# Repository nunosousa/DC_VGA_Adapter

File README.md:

# DC_VGA_Adapter
This is a project detailing a Dreamcast VGA circuit adapter to provide VGA video output.

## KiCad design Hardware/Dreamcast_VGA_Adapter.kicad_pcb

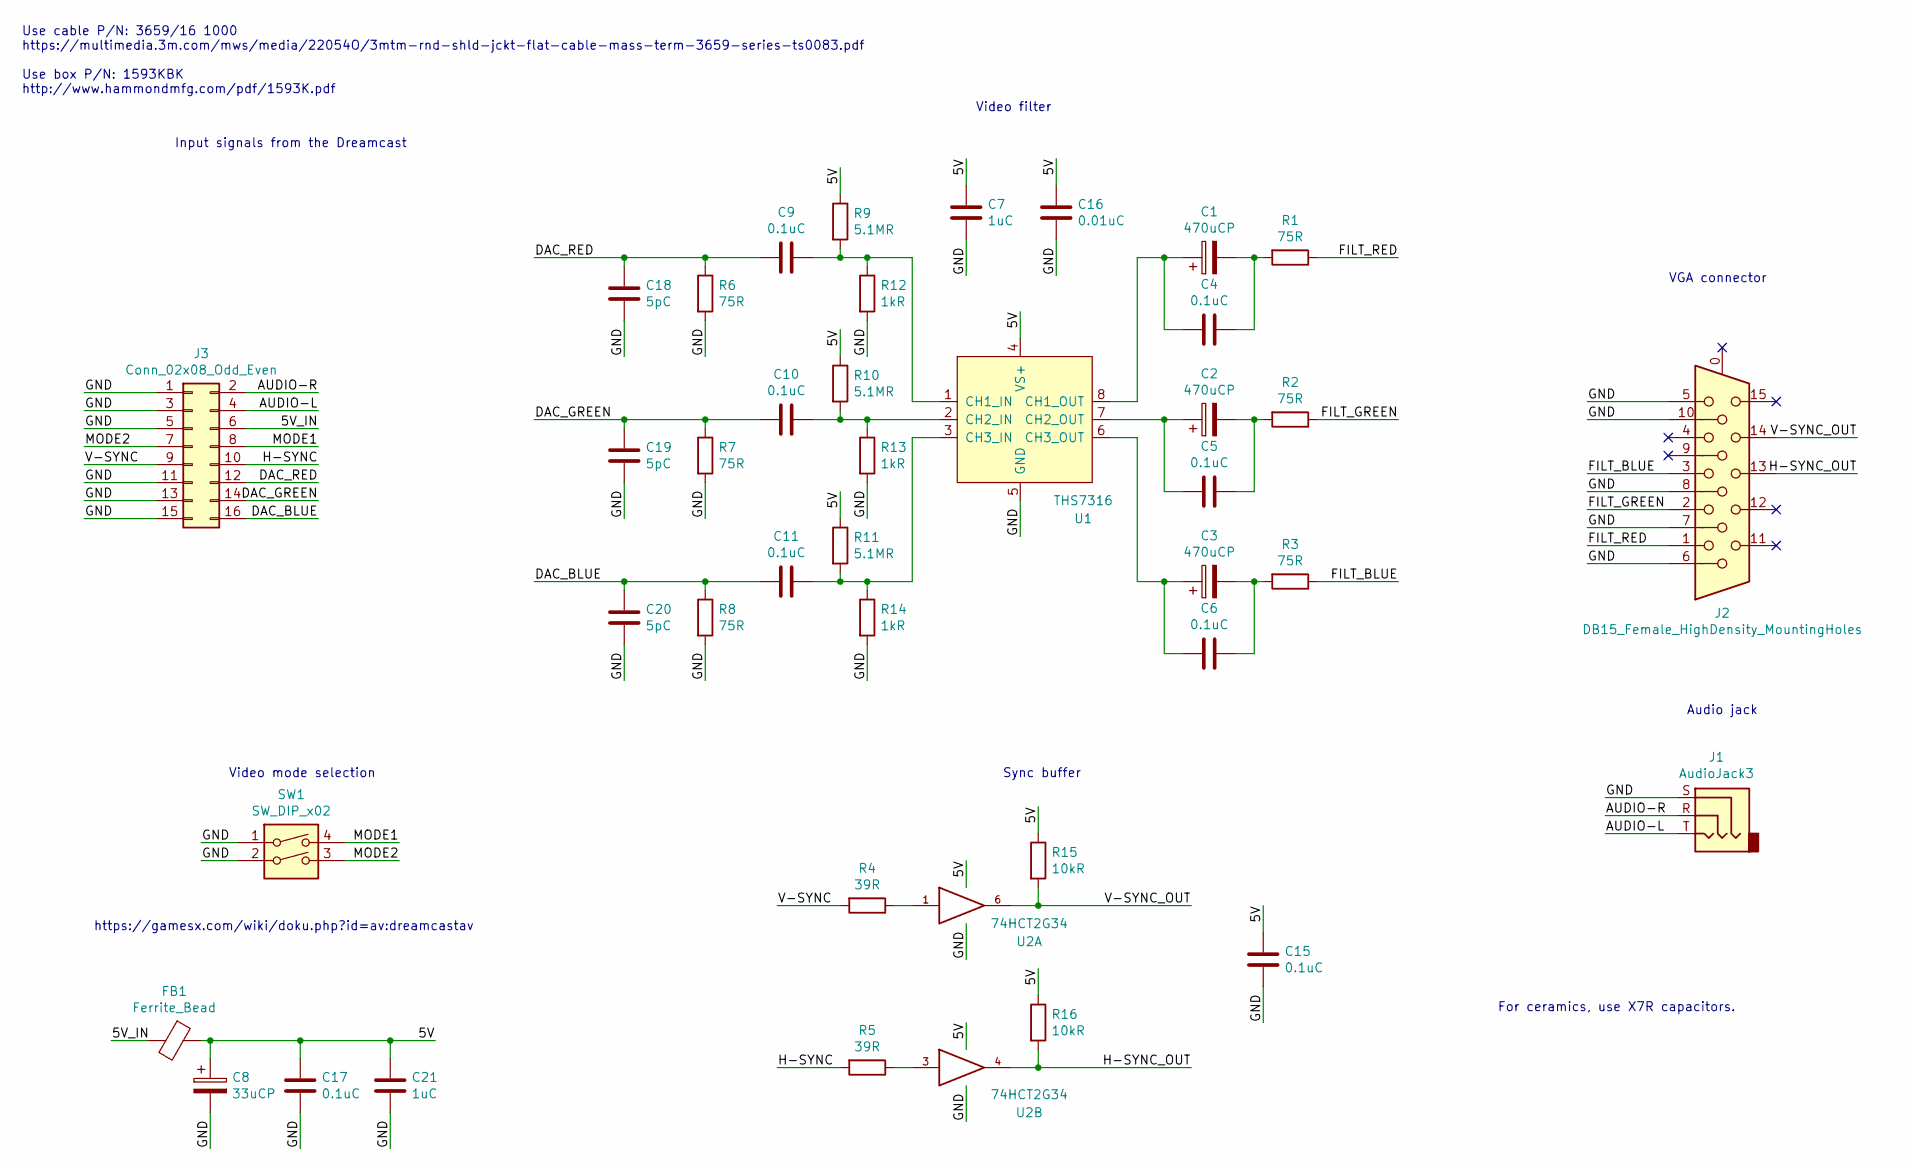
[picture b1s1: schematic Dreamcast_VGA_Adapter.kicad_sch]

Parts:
C1, C2, C3: 470uCP; CP_Radial_D8.0mm_P3.50mm; Manufacturer Part Number 16ZLH470MEFCT78X11.5
C4, C5, C6, C9, C10, C11, C15, C17: 0.1uC; C_0805_2012Metric_Pad1.15x1.40mm_HandSolder; Manufacturer Part Number AC0805KRX7R7BB104
C7, C21: 1uC; C_0805_2012Metric_Pad1.15x1.40mm_HandSolder; Manufacturer Part Number CC0805MKX7R7BB105
C8: 33uCP; CP_EIA-3528-21_Kemet-B_Pad1.50x2.35mm_HandSolder; Manufacturer Part Number TAJB336K006RNJ
C16: 0.01uC; C_0805_2012Metric_Pad1.15x1.40mm_HandSolder; Manufacturer Part Number CC0805KRX7R9BB103
C18, C19, C20: 5pC; C_0805_2012Metric_Pad1.15x1.40mm_HandSolder; Manufacturer Part Number 08055A5R0CAT2A
FB1: Ferrite_Bead; L_0805_2012Metric_Pad1.15x1.40mm_HandSolder; Manufacturer Part Number BLM21SP471SH1D
J1: AudioJack3; Jack_3.5mm_CUI_SJ1-3533NG_Horizontal; Manufacturer Part Number SJ1-3533NG
J2: DB15_Female_HighDensity_MountingHoles; DSUB-15-HD_Female_Horizontal_P2.29x1.98mm_EdgePinOffset3.03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; Manufacturer Part Number K61X-E15S-NJ
J3: Conn_02x08_Odd_Even; IDC-Header_2x08_P2.54mm_Vertical; Manufacturer Part Number 7816-0000PR
R1, R2, R3, R6, R7, R8: 75R; R_0805_2012Metric_Pad1.15x1.40mm_HandSolder; Manufacturer Part Number KTR10EZPF75R0
R4, R5: 39R; R_0805_2012Metric_Pad1.15x1.40mm_HandSolder; Manufacturer Part Number RC0805FR-0739RL
R9, R10, R11: 5.1MR; R_0805_2012Metric_Pad1.15x1.40mm_HandSolder; Manufacturer Part Number KTR10EZPF5104
R12, R13, R14: 1kR; R_0805_2012Metric_Pad1.15x1.40mm_HandSolder; Manufacturer Part Number RC0805FR-071KL
R15, R16: 10kR; R_0805_2012Metric_Pad1.15x1.40mm_HandSolder; Manufacturer Part Number RC0805FR-0710KL
SW1: SW_DIP_x02; SW_DIP_SPSTx02_Slide_9.78x7.26mm_W7.62mm_P2.54mm; Manufacturer Part Number DS01-254-L-02BE
U1: THS7316; SOIC-8_3.9x4.9mm_P1.27mm; Manufacturer Part Number THS7316DR
U2: 74HCT2G34; SOT-363_SC-70-6_Handsoldering; Manufacturer Part Number 74HCT2G34GW,125

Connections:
/5V_IN: FB1.2, J3.6
/AUDIO-L: J1.T, J3.4
/AUDIO-R: J1.R, J3.2
/DAC_BLUE: C11.2, C20.1, J3.16, R8.1
/DAC_GREEN: C10.2, C19.1, J3.14, R7.1
/DAC_RED: C9.2, C18.1, J3.12, R6.1
/FILT_BLUE: J2.3, R3.1
/FILT_GREEN: J2.2, R2.1
/FILT_RED: J2.1, R1.1
/H-SYNC: J3.10, R5.2
/H-SYNC_OUT: J2.13, R16.2, U2.4
/MODE1: J3.8, SW1.4
/MODE2: J3.7, SW1.3
/V-SYNC: J3.9, R4.2
/V-SYNC_OUT: J2.14, R15.2, U2.6
GND: C7.2, C8.2, C15.2, C16.2, C17.2, C18.2, C19.2, C20.2, C21.2, J1.S, J2.5, J2.6, J2.7, J2.8, J2.10, J3.1, J3.3, J3.5, J3.11, J3.13, J3.15, R6.2, R7.2, R8.2, R12.2, R13.2, R14.2, SW1.1, SW1.2, U1.5 (GND), U2.2 (GND)
unnamed: C1.1, C4.2, U1.8 (CH1_OUT)
unnamed: C1.2, C4.1, R1.2
unnamed: C2.1, C5.2, U1.7 (CH2_OUT)
unnamed: C2.2, C5.1, R2.2
unnamed: C3.1, C6.2, U1.6 (CH3_OUT)
unnamed: C3.2, C6.1, R3.2
unnamed: C9.1, R9.2, R12.1, U1.1 (CH1_IN)
unnamed: C10.1, R10.2, R13.1, U1.2 (CH2_IN)
unnamed: C11.1, R11.2, R14.1, U1.3 (CH3_IN)
unnamed: R4.1, U2.1
unnamed: R5.1, U2.3
VCC: C7.1, C8.1, C15.1, C16.1, C17.1, C21.1, FB1.1, R9.1, R10.1, R11.1, R15.1, R16.1, U1.4 (VS+), U2.5 (VCC)

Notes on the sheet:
Video mode selection
Video filter
For ceramics, use X7R capacitors.
Audio jack
Use cable P/N: 3659/16 1000 https://multimedia.3m.com/mws/media/22054O/3mtm-rnd-shld-jckt-flat-cable-mass-term-3659-series-ts0083.pdf Use box P/N: 1593KBK http://www.hammondmfg.com/pdf/1593K.pdf
Sync buffer
Input signals from the Dreamcast
https://gamesx.com/wiki/doku.php?id=av:dreamcastav
VGA connector

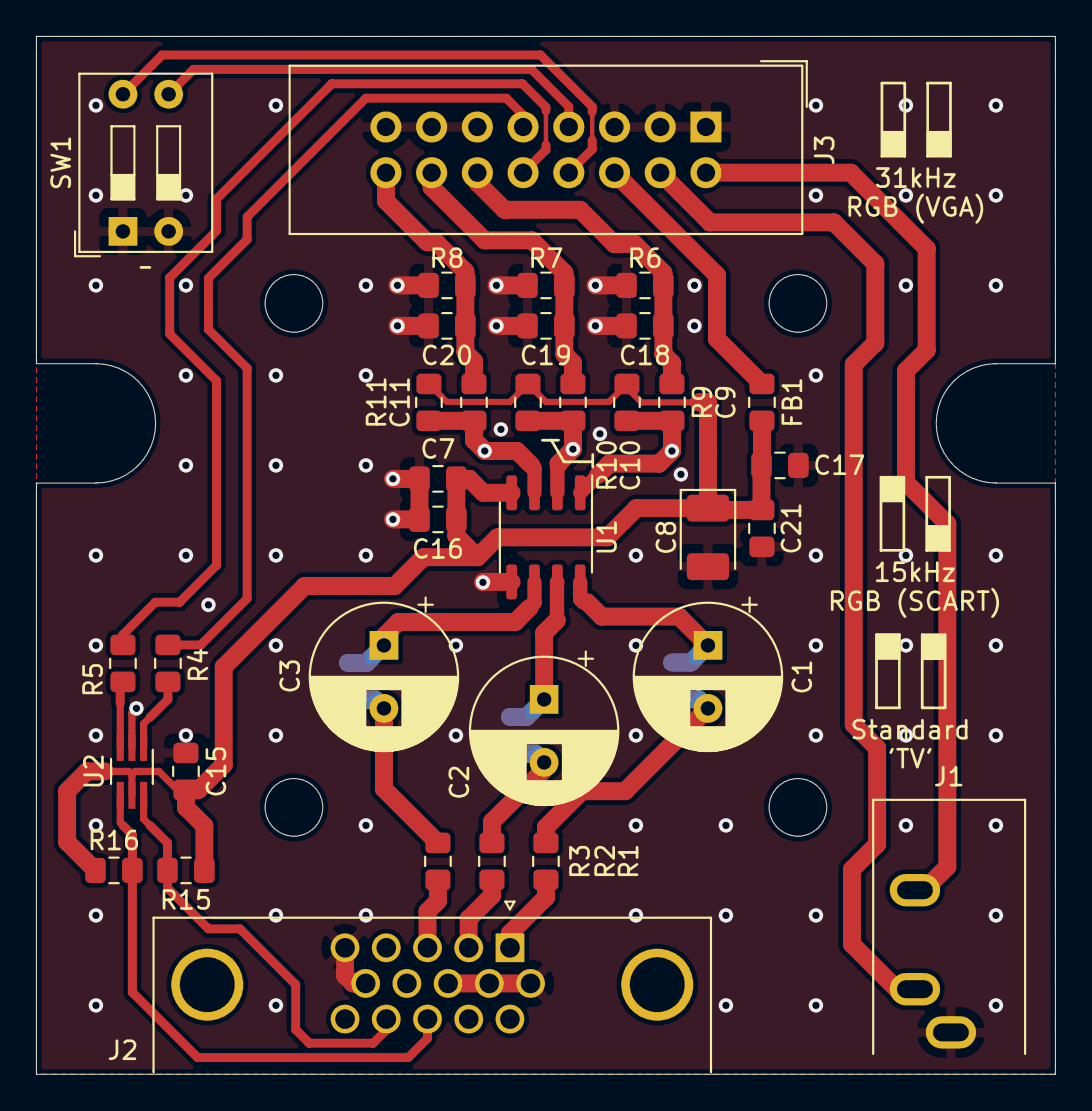
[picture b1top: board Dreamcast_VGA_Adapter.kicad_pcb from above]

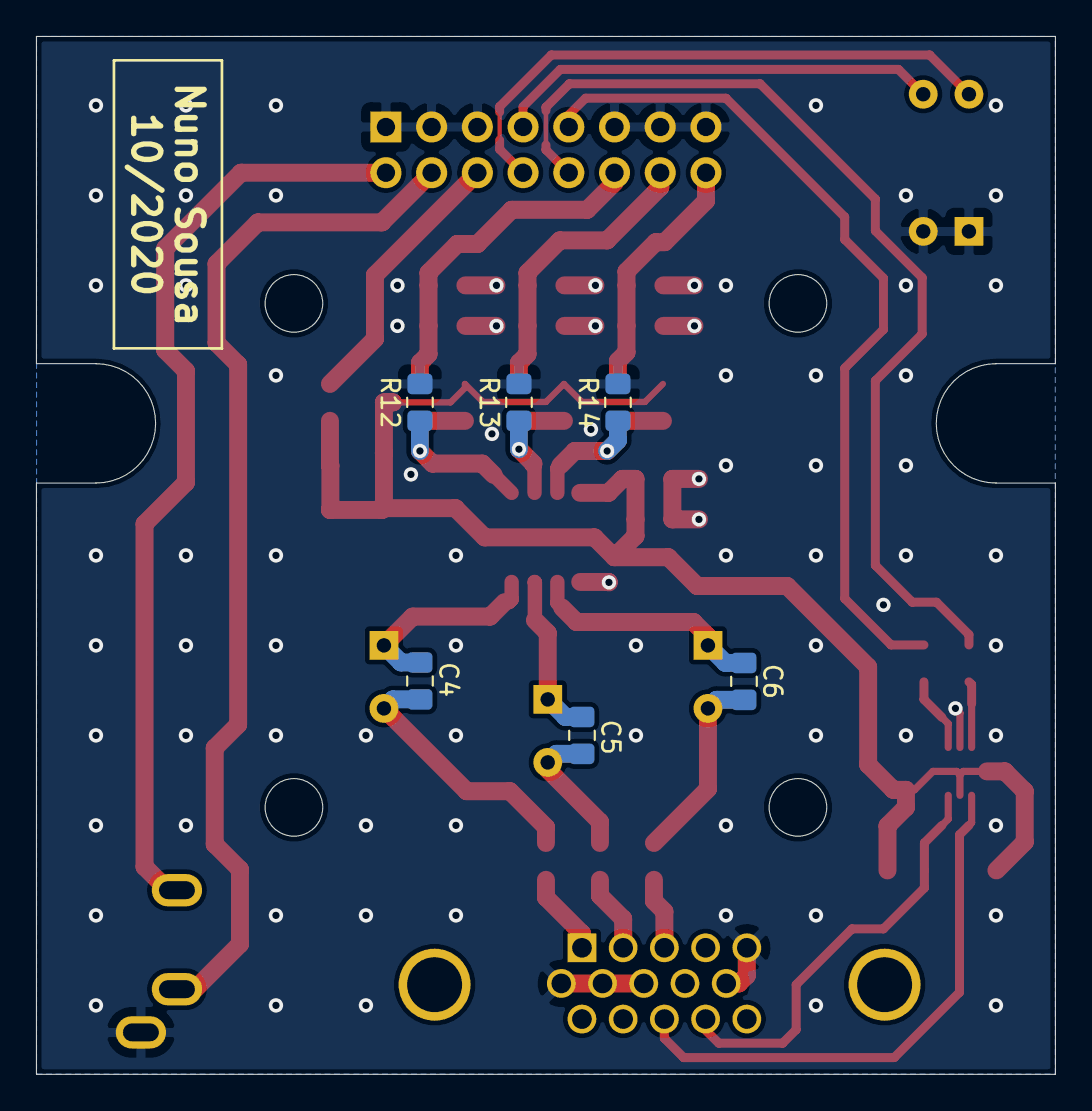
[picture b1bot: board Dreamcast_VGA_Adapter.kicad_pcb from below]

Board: 2 copper layers, 56.6 x 57.7 mm, 41 parts (6 on the bottom side), 28 nets.

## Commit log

2020-09-19 Initial commit.
2020-10-07 Progressed circuit design.
2020-10-09 Generated gerbers.
2020-10-10 Created 3D model
2020-10-10 Updated 3d model.
2020-10-10 Revert "Updated 3d model."
    This reverts commit c74a3e178eb67756c56d84720efd85ba3459a0e9.
2020-10-10 Revert "Created 3D model"
    This reverts commit 1b23ede2aa55525ab1088a1304cc43113caee66c.
2020-10-10 Moved audio jack.
2020-10-10 Created 3D assembly.
2020-10-10 Progressed 3D model.
2020-10-10 Updated 3D design.
2020-10-10 Updated PCB.
2020-10-10 Updated 3D assembly.
2024-04-14 Upgraded from Kicad 5 to Kicad 8.
